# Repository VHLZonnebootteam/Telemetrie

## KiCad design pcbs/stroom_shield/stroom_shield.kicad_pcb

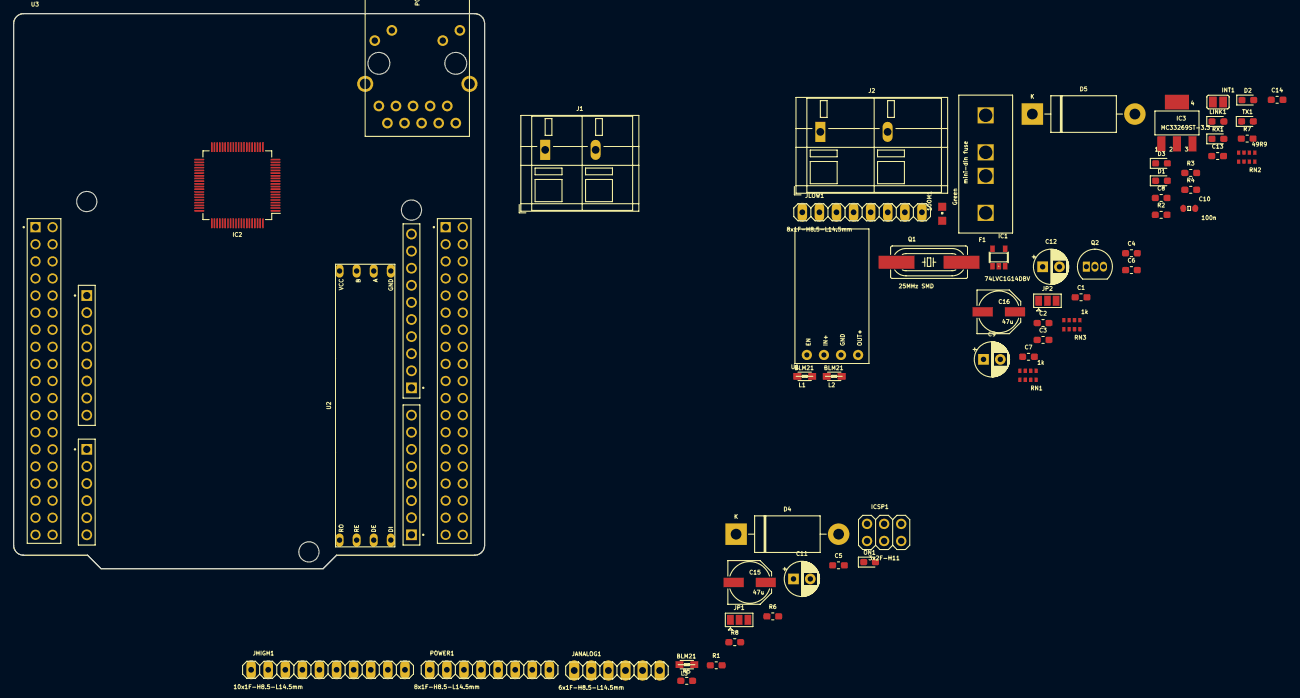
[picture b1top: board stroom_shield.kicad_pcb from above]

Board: 2 copper layers, 70.0 x 82.5 mm, 60 parts (0 on the bottom side), 40 nets, no tracks yet.

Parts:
100M1: Green; LED_CHIPLED_0805
C1, C2, C3, C6, C7, C13: 100n; R_0603_1608Metric_Pad1.05x0.95mm_HandSolder
C4, C5: 22p; R_0603_1608Metric_Pad1.05x0.95mm_HandSolder
C8: 10u; R_0603_1608Metric_Pad1.05x0.95mm_HandSolder
C9, C11, C12: 470uf; CP_Radial_D5.0mm_P2.50mm
C10: 100n; SMARTPRJ_C0603-ROUND
C14: 10uf; C_0603_1608Metric_Pad1.05x0.95mm_HandSolder
C15, C16: 47u; RCL_PANASONIC_D
D1: OK; LED_0603_1608Metric_Pad1.05x0.95mm_HandSolder
D2: INIT; LED_0603_1608Metric_Pad1.05x0.95mm_HandSolder
D3: PWR; LED_0603_1608Metric_Pad1.05x0.95mm_HandSolder
D4, D5: 1N5401; D_DO-201AD_P15.24mm_Horizontal
F1: Fuse; fuse_holder
IC1: 74LVC1G14DBV; 74XX-LITTLE-DE_SOT23-5
IC2: W5100; LQFP-80_10x10mm_P0.4mm
IC3: MC33269ST-3.3; LINEAR_SOT223
ICSP1: 3x2F-H11; SMARTPRJ_2X03
INT1: JUMPER_SJ
J1: 12V in; TerminalBlock_WAGO_236-202_1x02_P7.50mm_45Degree
J2: 10V out; TerminalBlock_WAGO_236-302_1x02_P10.00mm_45Degree
JANALOG1: 6x1F-H8.5-L14.5mm; PINHEAD_1X06
JHIGH1: 10x1F-H8.5-L14.5mm; SMARTPRJ_1X10
JLOW1: 8x1F-H8.5-L14.5mm; SMARTPRJ_1X08
JP1, JP2: Jumper_NC_Dual; SolderJumper-3_P1.3mm_Open_Pad1.0x1.5mm
L1, L2, L3: BLM21; WUERTH-ELEKTRONIK_0805
LINK1: Yellow; LED_0603_1608Metric_Pad1.05x0.95mm_HandSolder
ON1: Green; LED_0603_1608Metric_Pad1.05x0.95mm_HandSolder
POWER1: 8x1F-H8.5-L14.5mm; SMARTPRJ_1X08
Q1: 25MHz SMD; CRYSTAL_HC49UP
Q2: PN2222A; TO-92_Inline
R1, R4: 10k; R_0603_1608Metric_Pad1.05x0.95mm_HandSolder
R2: 300R 1%; R_0603_1608Metric_Pad1.05x0.95mm_HandSolder
R3: 12k 1%; R_0603_1608Metric_Pad1.05x0.95mm_HandSolder
R5: 1M; R_0603_1608Metric_Pad1.05x0.95mm_HandSolder
R6, R7, R8: 1K; R_0603_1608Metric_Pad1.05x0.95mm_HandSolder
RN1, RN3: 1k; RESISTOR-DIL_CAY16
RN2: 49R9; RESISTOR-DIL_CAY16
RX1: Yellow; LED_0603_1608Metric_Pad1.05x0.95mm_HandSolder
TX1: Yellow; LED_0603_1608Metric_Pad1.05x0.95mm_HandSolder
U1: buck_converter
U2: RS485_module
U3: NUCLEO-F446RE; MODULE_NUCLEO-F446RE
U$1: POE-RJ45; SMARTPRJ_POE-RJ45

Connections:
+3V3: C6.1, C7.1, C16.+, IC1.5, IC2.12, IC2.18, IC2.44, IC3.2, IC3.4, L3.2, R1.1, R4.2, RN1.1, RN1.2, RN1.3, RN1.4, RN3.1, RN3.2, RN3.4
+5V: C9.1, C11.1, C14.1, C15.+, IC3.3, ICSP1.2, POWER1.5, U1.4, U3.CN6_5, U3.CN7_18
+10V: C12.1, F1.1, J2.2, U1.1, U1.2
/+1V8: IC2.11, IC2.15, IC2.16, IC2.33, IC2.69, L2.1
/+1V8A: IC2.7, IC2.74, L2.2
/+3V3A: C1.1, C10.1, C13.1, IC2.2, L3.1, U$1.R3
/INT: IC2.56, INT1.1
/LINKLED: IC2.66, U$1.L4
/MISO: IC2.27, ICSP1.1
/MOSI: IC2.28, ICSP1.4
/N$2: RN1.5, U$1.L3
/N$3: RN1.8, U$1.L1
/N$10: C3.2, RN2.3, RN2.4
/N$25: 100M1.A, RN3.7
/N$29: C2.2, RN2.1, RN2.2
/N$30: R2.1, R3.2
/N$31: IC2.1, R3.1
/N$36: IC2.55, IC2.57, IC2.58, R4.1
/OSC1E: C4.1, IC2.76, Q1.1, R5.1
/OSC2E: C5.1, IC2.75, Q1.2, R5.2
/PD2: INT1.2, JLOW1.3
/RXIN: IC2.6, RN2.7, U$1.R2
/RXIP: IC2.5, RN2.8, U$1.R1
/SCK: IC2.30, ICSP1.3
/SEN: IC1.4, IC2.31, R1.2
/SH: L1.2, U$1.CH1, U$1.CH2
/SPDLED: 100M1.C, IC2.67, U$1.L2
/SS: IC1.2, IC2.29, JHIGH1.3
/TXON: IC2.9, RN2.5, U$1.R4
/TXOP: IC2.8, RN2.6, U$1.R5
GND: C1.2, C2.1, C3.1, C4.2, C5.2, C6.2, C7.2, C9.2, C10.2, C11.2, C12.2, C13.2, C14.2, C15.-, C16.-, D1.1, D2.1, D3.1, D5.2, IC1.3, IC2.4, IC2.10, IC2.13, IC2.14, IC2.17, IC2.19, IC2.20, IC2.21, IC2.22, IC2.23, IC2.24, IC2.25, IC2.26, IC2.32, IC2.34, IC2.35, IC2.36, IC2.37, IC2.38, IC2.39, IC2.40, IC2.41, IC2.42, IC2.43, IC2.45, IC2.46, IC2.47, IC2.48, IC2.49, IC2.50, IC2.51, IC2.52, IC2.53, IC2.54, IC2.63, IC2.64, IC2.65, IC2.68, IC2.77, IC3.1, ICSP1.6, J2.1, JHIGH1.7, L1.1, POWER1.6, POWER1.7, R2.2, U1.3, U3.CN5_7, U3.CN6_6, U3.CN6_7, U3.CN7_8, U3.CN7_19, U3.CN7_20, U3.CN7_22, U3.CN10_9, U3.CN10_20
unnamed: D1.2, R6.1
unnamed: D2.2, R7.1
unnamed: D3.2, R8.1
unnamed: D4.1, F1.2
unnamed: D4.2, J1.2
unnamed: D5.1, J1.1
indicator_green: R6.2, U3.CN9_5
indicator_red: R8.2, U3.CN9_3
indicator_yellow: R7.2, U3.CN9_4

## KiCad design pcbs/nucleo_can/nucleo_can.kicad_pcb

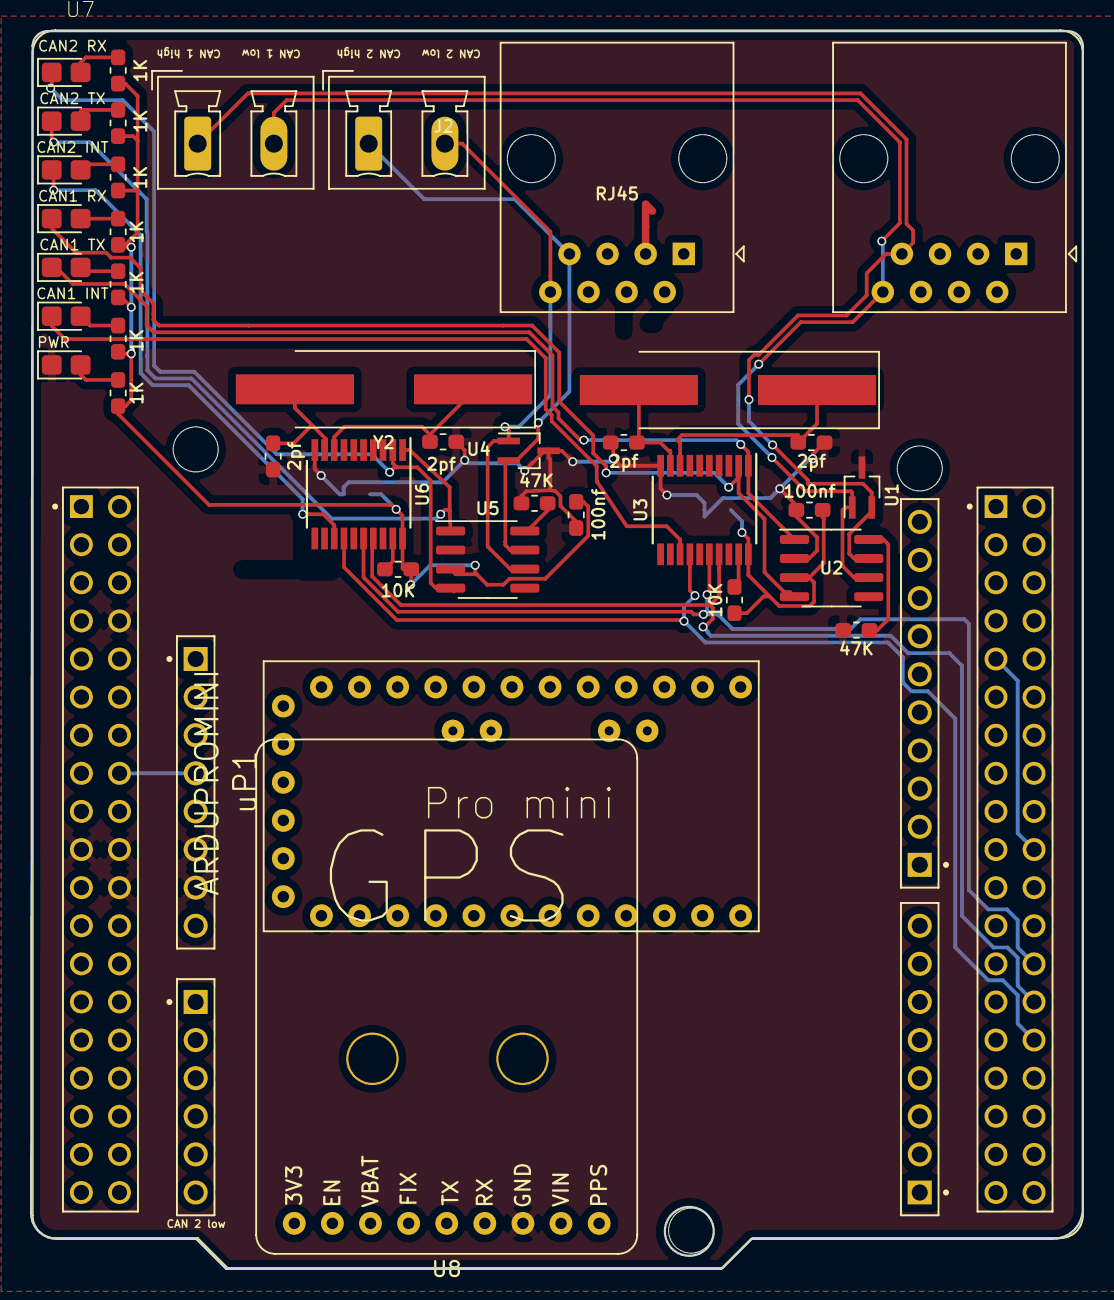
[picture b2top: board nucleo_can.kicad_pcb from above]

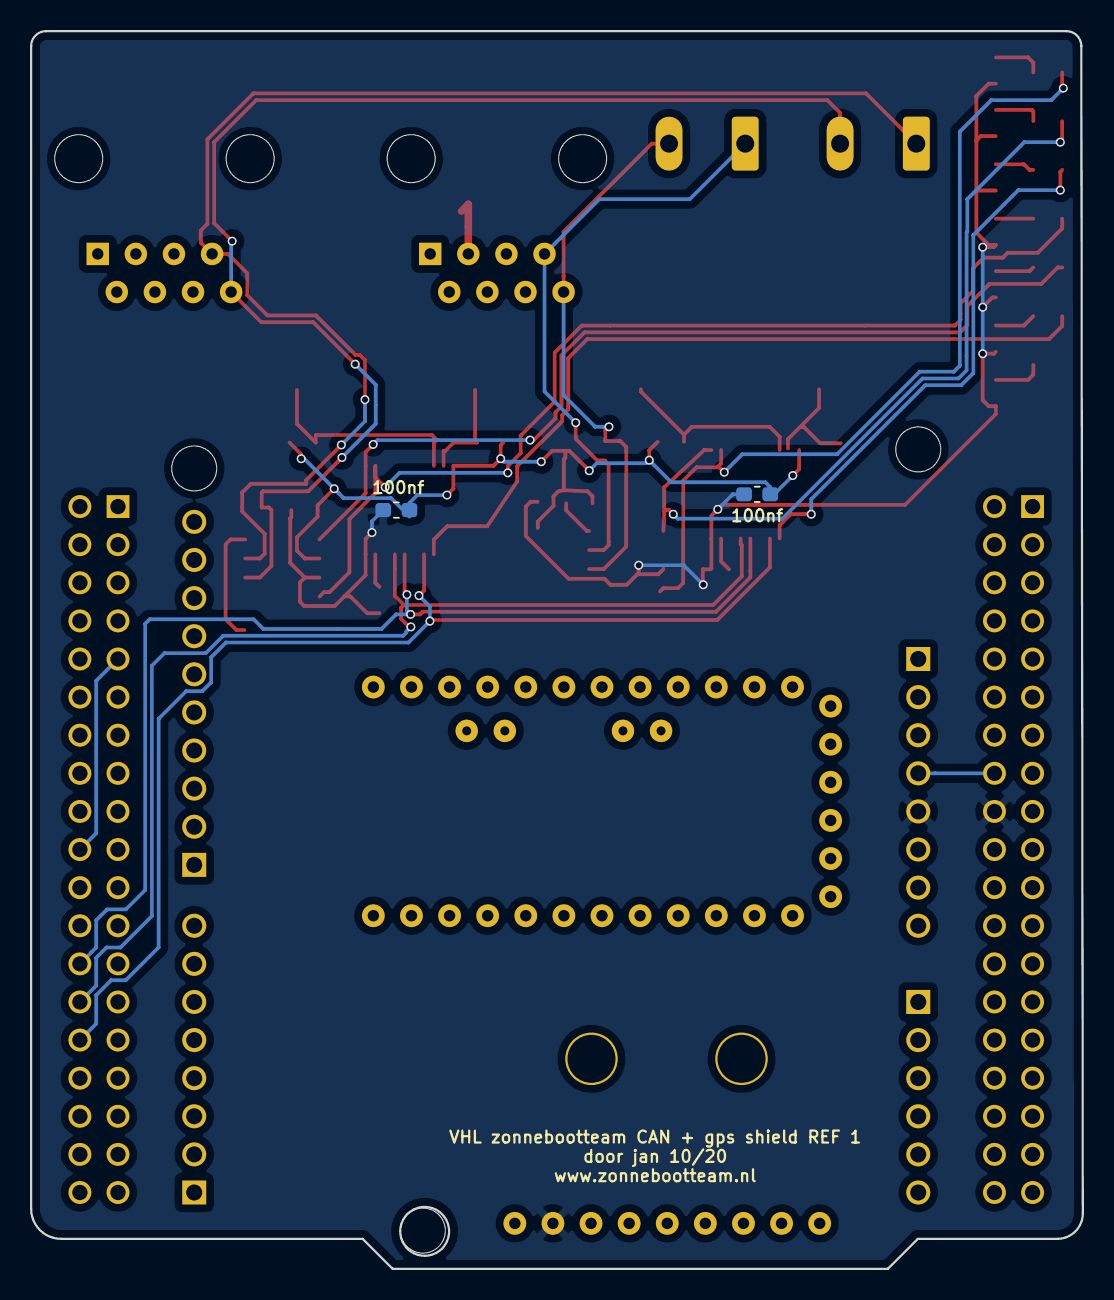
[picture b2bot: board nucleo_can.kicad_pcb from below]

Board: 2 copper layers, 70.1 x 82.5 mm, 41 parts (2 on the bottom side), 34 nets.

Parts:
C1, C4, C5, C6: 100nf; C_0603_1608Metric_Pad1.05x0.95mm_HandSolder
C2, C3, C7, C8: 2pf; C_0603_1608Metric_Pad1.05x0.95mm_HandSolder
D1, D2, D3, D4, D5, D6, D7: LED; LED_0805_2012Metric_Castellated
J1, J2: RJ45; RJ45_Amphenol_54602-x08_Horizontal
J4, J5: Screw_Terminal_01x02; PhoenixContact_MCV_1,5_2-G-5.08_1x02_P5.08mm_Vertical
R1, R10: 47K; R_0603_1608Metric_Pad1.05x0.95mm_HandSolder
R2, R11: 10K; R_0603_1608Metric_Pad1.05x0.95mm_HandSolder
R3, R4, R5, R6, R7, R8, R9: 1K; R_0603_1608Metric_Pad1.05x0.95mm_HandSolder
U1, U4: PESD5V0L2UU_esd_diode; SOT-323_SC-70_Handsoldering
U2, U5: MCP2551-I-SN; SOIC-8_3.9x4.9mm_P1.27mm
U3, U6: MCP2515-xST; TSSOP-20_4.4x6.5mm_P0.65mm
U7: NUCLEO-F446RE; MODULE_NUCLEO-F446RE
U8: adafruit_gps_module; gps_module
Y1, Y2: Crystal; Crystal_SMD_HC49-SD_HandSoldering
uP1: ARDUPROMINI; ArduProMini

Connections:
+3V3: U7.CN6_4, U7.CN7_16
+5V: C1.1, C4.1, C5.1, C6.1, R2.2, R3.1, R4.1, R5.1, R6.1, R7.1, R8.1, R9.1, R11.2, U2.3, U3.20, U5.3, U6.20, U7.CN6_5, U7.CN7_18, U8.8
CAN_INTR_1_1: D4.1, U3.13
CAN_INTR_2: D7.1, U6.13
CAN_RX_1: D3.1, U2.4, U3.2
CAN_RX_2: D6.1, U5.4, U6.2
CAN_TX_1: D2.1, U2.1, U3.1
CAN_TX_2: D5.1, U5.1, U6.1
GND: C1.2, C2.1, C3.1, C4.2, C5.2, C6.2, C7.1, C8.1, D1.1, R1.1, R10.1, U1.3, U2.2, U3.10, U4.3, U5.2, U6.10, U7.CN6_6, U7.CN6_7, U7.CN7_8, U7.CN7_19, U7.CN7_20, U7.CN7_22, U8.7
unnamed: C2.2, U3.8, Y1.1
unnamed: C3.2, U3.9, Y1.2
unnamed: C7.2, U6.8, Y2.1
unnamed: C8.2, U6.9, Y2.2
unnamed: D1.2, R3.2
unnamed: D2.2, R4.2
unnamed: D3.2, R5.2
unnamed: D4.2, R6.2
unnamed: D5.2, R7.2
unnamed: D6.2, R8.2
unnamed: D7.2, R9.2
unnamed: R1.2, U2.8
unnamed: R2.1, U3.19
unnamed: R10.2, U5.8
unnamed: R11.1, U6.19
unnamed: U7.CN10_9, U7.CN10_20
SPI2_CLK: U3.14, U6.14, U7.CN10_30
SPI2_MISO: U3.17, U6.17, U7.CN10_28
SPI2_MOSI: U3.16, U6.16, U7.CN10_26
UART_6_RX: U7.CN10_12, U8.5
UART_6_TX: U7.CN10_14, U8.6
can_h_1: J1.7, J4.1, U1.2, U2.7
can_h_2: J2.7, J5.1, U4.2, U5.7
can_l_1: J1.8, J4.2, U1.1, U2.6
can_l_2: J2.8, J5.2, U4.1, U5.6

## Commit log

2023-09-13 add everything
2025-06-11 Telemetry over wifi esp32
    dit kunnen we gebruiken als de router of Arduino toren niet werkt.
